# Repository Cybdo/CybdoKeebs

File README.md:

# CybdoKeebs!

A hotswappable ecosystem of i2c powered keyboard modules!

I made this project because I wanted to make something cooler than a macropad, and being able to just swap stuff around seemed really sick.

Inspired by [Ocreeb](https://www.youtube.com/watch?v=7DfexfHzT-w)!

# File structure

everything for each module is found under `modules/[module name]`, including CAD files, EDA files and firmware.

# Features
 - plug and play
 - hotswappable modules
 - exposed I2C buses
 - fully open source!
 - supports any MX-footprint keyswitches!
 - inbuilt USB hub in the controller

# Firmware
Firmware runs on circuitpython, and the firmware for each module is under `modules/[module name]/firmware`. Flash it using the SWD ports on each module, or via USB on the controller hub. You may need a SWD to USB converter, which can be made using a Raspberry Pi Pico.

# Custom modules
Each module is made as a composite of "sub units", each being 6cm tall and 5cm wide, with male pogo pins on the top and left sides, and female recievers on the bottom and right sides. These can be found here: https://www.aliexpress.com/item/1005005284441979.html

# Assembly
Everything is designed to be tray mounted, as to not obstruct the pogo pin assemblies! This means, the plate snaps into and are held up by keyswitches.

To put the keyboard together, put 4 keyswitches in each of the corners of the plate, then put the keyswitches through their sockets. After checking that everything is aligned, put in the rest of the switches!

# BOM
found at `bom.csv`, assuming 1 controller hub, one keyboard and one macropad

# Schematics

## Hub

## Macropad

## Keyboard

# PCB

## Hub

## Macropad

## Keyboard

# Acknowledgements
 - [KiCad](https://www.kicad.org)
 - [Hack Club Fallout](https://fallout.hackclub.com)
 - [Ocreeb V2](https://github.com/sb-ocr/ocreeb-mk-2)
 - [CircuitPython](https://circuitpython.org/)
 - [ai03 Plate Generator](https://kbplate.ai03.com/)
 - [Hack Club Hackpad](https://hackpad.hackclub.com)

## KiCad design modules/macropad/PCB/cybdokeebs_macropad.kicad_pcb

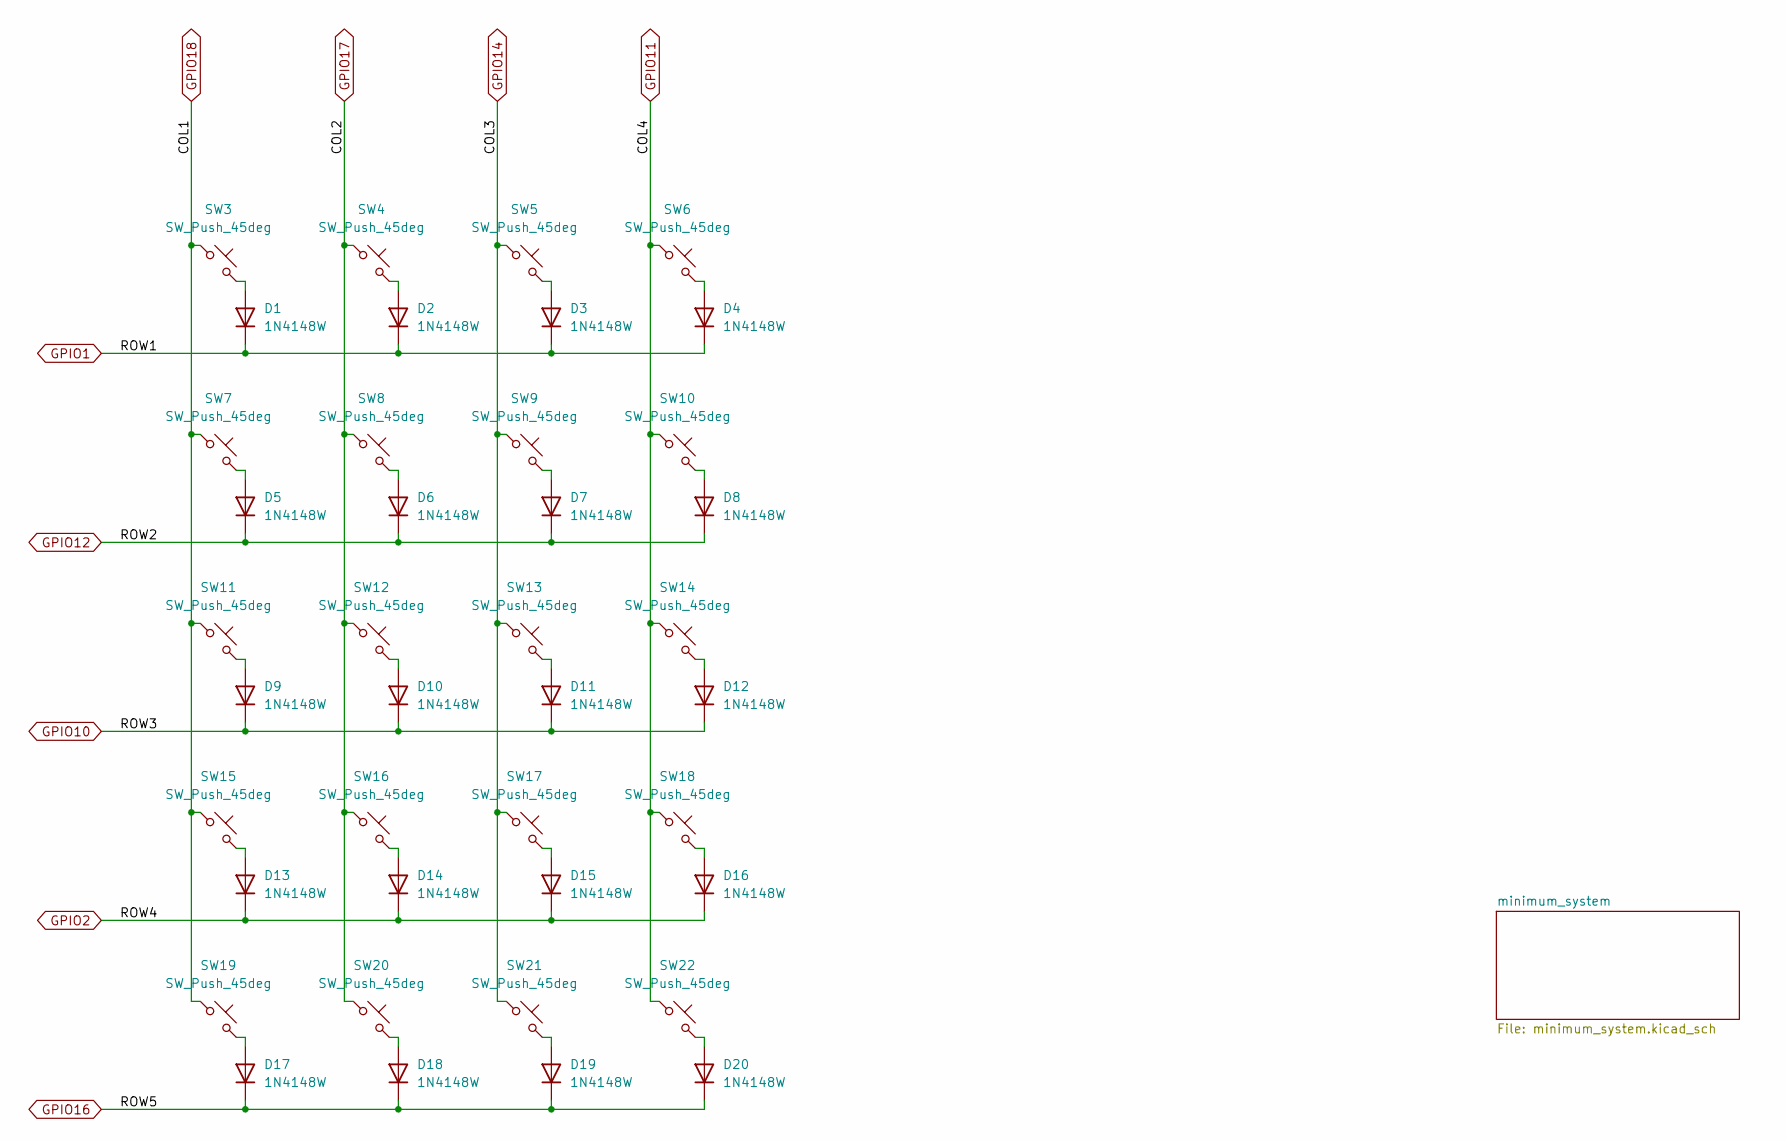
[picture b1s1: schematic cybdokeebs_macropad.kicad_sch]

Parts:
D1, D2, D3, D4, D5, D6, D7, D8, D9, D10, D11, D12, D13, D14, D15, D16, D17, D18, D19, D20: 1N4148W; D_SOD-123
SW3, SW4, SW5, SW6, SW7, SW8, SW9, SW10, SW11, SW12, SW13, SW14, SW15, SW16, SW17, SW18, SW19, SW20, SW21, SW22: SW_Push_45deg; SW_Hotswap_Kailh_MX_1.00u

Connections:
GPIO1: D1.1 (K), D2.1 (K), D3.1 (K), D4.1 (K); also elsewhere on the board
GPIO2: D13.1 (K), D14.1 (K), D15.1 (K), D16.1 (K); also elsewhere on the board
GPIO10: D9.1 (K), D10.1 (K), D11.1 (K), D12.1 (K); also elsewhere on the board
GPIO11: SW6.1, SW10.1, SW14.1, SW18.1, SW22.1; also elsewhere on the board
GPIO12: D5.1 (K), D6.1 (K), D7.1 (K), D8.1 (K); also elsewhere on the board
GPIO14: SW5.1, SW9.1, SW13.1, SW17.1, SW21.1; also elsewhere on the board
GPIO16: D17.1 (K), D18.1 (K), D19.1 (K), D20.1 (K); also elsewhere on the board
GPIO17: SW4.1, SW8.1, SW12.1, SW16.1, SW20.1; also elsewhere on the board
GPIO18: SW3.1, SW7.1, SW11.1, SW15.1, SW19.1; also elsewhere on the board
unnamed: D1.2 (A), SW3.2
unnamed: D2.2 (A), SW4.2
unnamed: D3.2 (A), SW5.2
unnamed: D4.2 (A), SW6.2
unnamed: D5.2 (A), SW7.2
unnamed: D6.2 (A), SW8.2
unnamed: D7.2 (A), SW9.2
unnamed: D8.2 (A), SW10.2
unnamed: D9.2 (A), SW11.2
unnamed: D10.2 (A), SW12.2
unnamed: D11.2 (A), SW13.2
unnamed: D12.2 (A), SW14.2
unnamed: D13.2 (A), SW15.2
unnamed: D14.2 (A), SW16.2
unnamed: D15.2 (A), SW17.2
unnamed: D16.2 (A), SW18.2
unnamed: D17.2 (A), SW19.2
unnamed: D18.2 (A), SW20.2
unnamed: D19.2 (A), SW21.2
unnamed: D20.2 (A), SW22.2

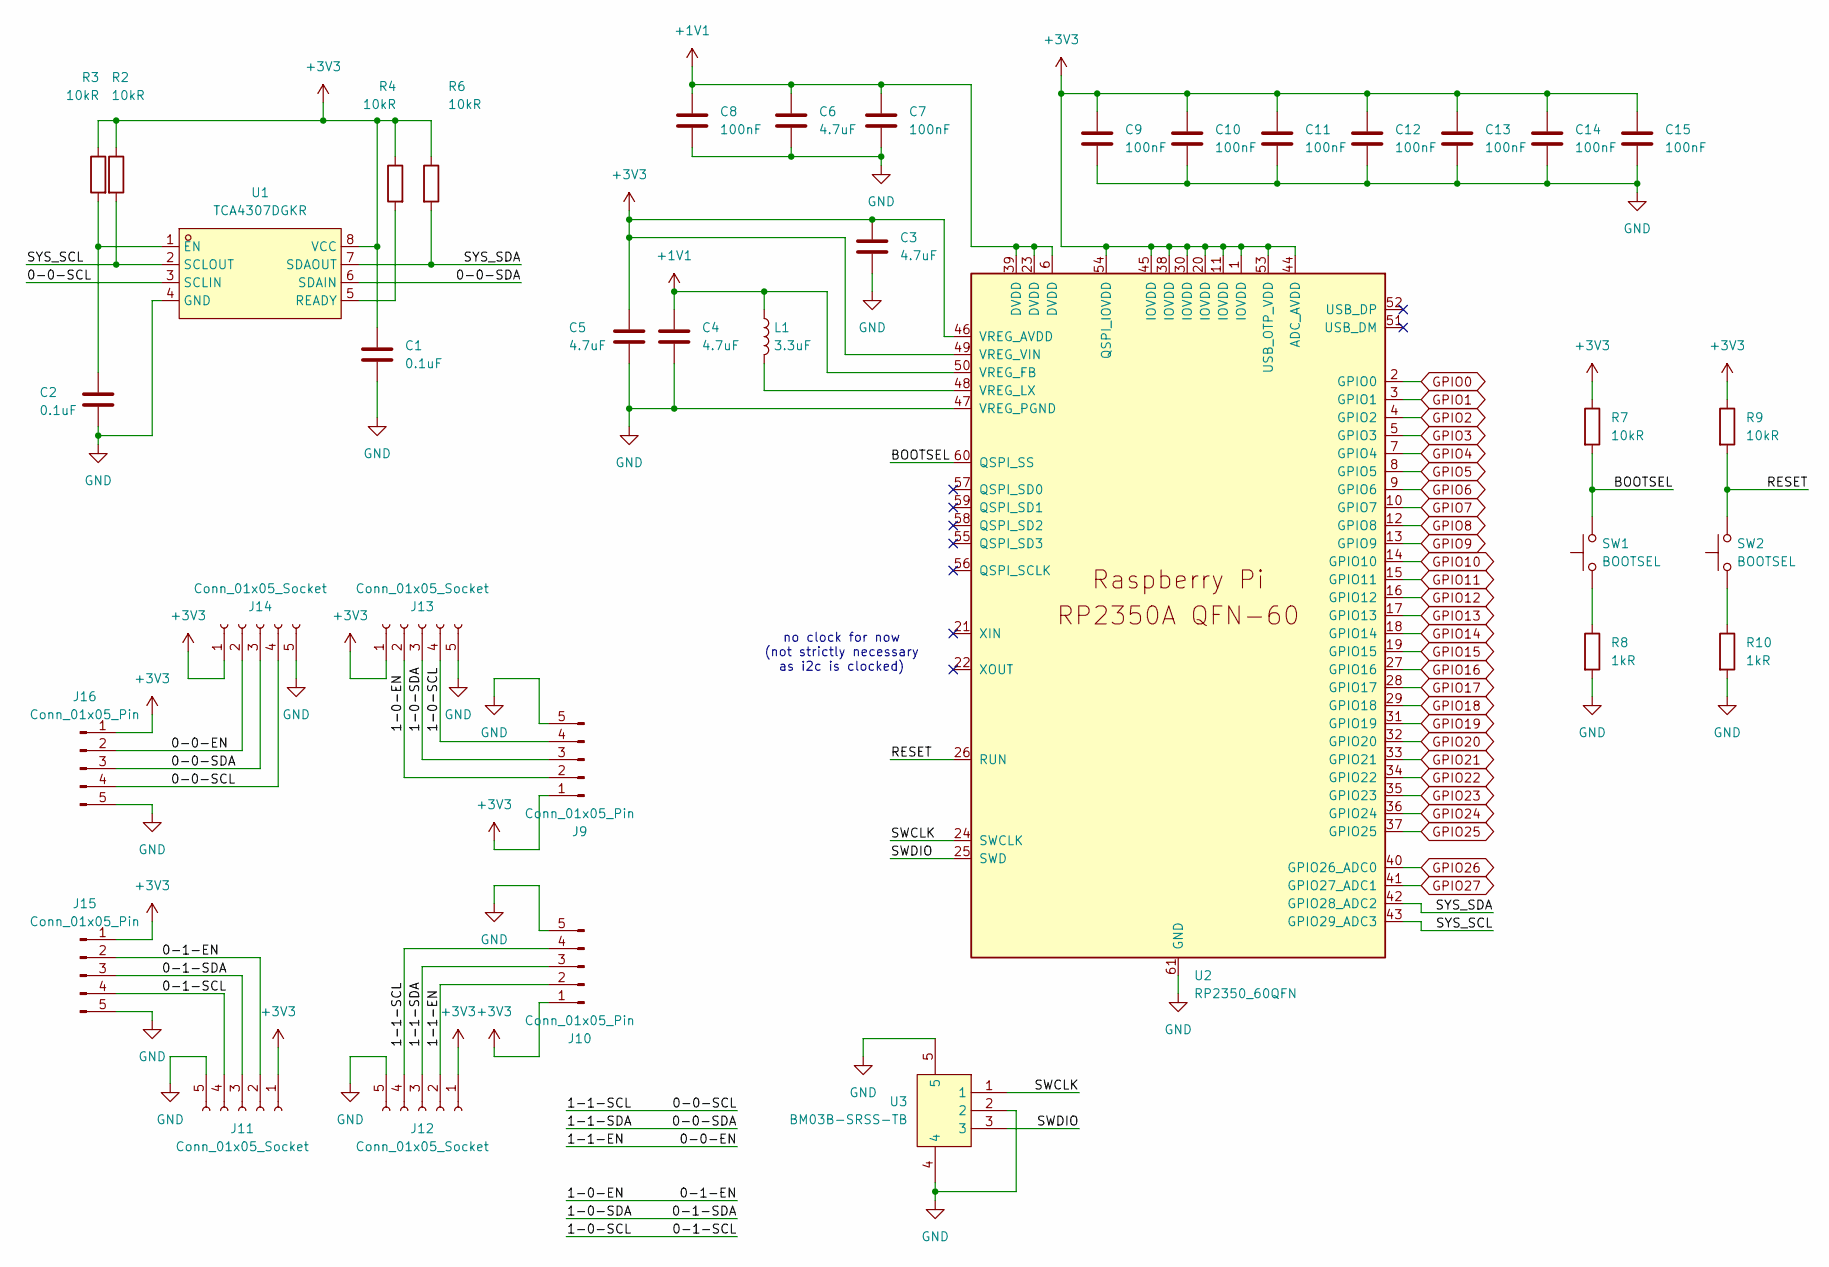
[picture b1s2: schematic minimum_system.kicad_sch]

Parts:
C1, C2: 0.1uF; C_0402_1005Metric_Pad0.74x0.62mm_HandSolder
C3, C4, C5, C6: 4.7uF; C_0402_1005Metric_Pad0.74x0.62mm_HandSolder
C7, C8, C9, C10, C11, C12, C13, C14, C15: 100nF; C_0402_1005Metric_Pad0.74x0.62mm_HandSolder
J9, J10, J15, J16: Conn_01x05_Pin; pogo 5pin 2.54
J11, J12, J13, J14: Conn_01x05_Socket; pogo 5pin 2.54
L1: 3.3uF; INDC1608X95N
R2, R3, R4, R6, R7, R9: 10kR; R_0402_1005Metric_Pad0.72x0.64mm_HandSolder
R8, R10: 1kR; R_0402_1005Metric_Pad0.72x0.64mm_HandSolder
SW1, SW2: BOOTSEL; SW_Push_SPST_NO_Alps_SKRK
U1: TCA4307DGKR; VSSOP-8_L3.0-W3.0-P0.65-LS4.9-BL; MPN TCA4307DGKR; LCSC Part C880333
U2: RP2350_60QFN; RP2350-QFN-60-1EP_7x7_P0.4mm_EP3.4x3.4mm_ThermalVias
U3: BM03B-SRSS-TB; CONN-SMD-3P-P1.00_BM03B-SRSS-TB-LF-SN; MPN BM03B-SRSS-TB(LF)(SN); LCSC Part C160389

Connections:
+1V1: C4.1, C6.1, C7.2, C8.1, L1.1, U2.6 (DVDD), U2.23 (DVDD), U2.39 (DVDD), U2.50 (VREG_FB)
+3V3: C1.1, C3.1, C5.2, C9.2, C10.2, C11.2, C12.2, C13.2, C14.2, C15.2, J9.1, J10.1, J11.1, J12.1, J13.1, J14.1, J15.1, J16.1, R2.1, R3.1, R4.1, R6.1, R7.1, R9.1, U1.8 (VCC), U2.1 (IOVDD), U2.11 (IOVDD), U2.20 (IOVDD), U2.30 (IOVDD), U2.38 (IOVDD), U2.44 (ADC_AVDD), U2.45 (IOVDD), U2.46 (VREG_AVDD), U2.49 (VREG_VIN), U2.53 (USB_OTP_VDD), U2.54 (QSPI_IOVDD)
/minimum_system/0-0-SCL: J10.4, J12.4, J14.4, J16.4, U1.3 (SCLIN)
/minimum_system/0-0-SDA: J10.3, J12.3, J14.3, J16.3, U1.6 (SDAIN)
/minimum_system/0-1-EN: J9.2, J11.2, J13.2, J15.2
/minimum_system/0-1-SCL: J9.4, J11.4, J13.4, J15.4
/minimum_system/0-1-SDA: J9.3, J11.3, J13.3, J15.3
/minimum_system/BOOTSEL: R7.2, SW1.2, U2.60 (QSPI_SS)
/minimum_system/RESET: R9.2, SW2.2, U2.26 (RUN)
/minimum_system/SWCLK: U2.24 (SWCLK), U3.1
/minimum_system/SWDIO: U2.25 (SWD), U3.3
/minimum_system/SYS_SCL: R2.2, U1.2 (SCLOUT), U2.43 (GPIO29_ADC3)
/minimum_system/SYS_SDA: R6.2, U1.7 (SDAOUT), U2.42 (GPIO28_ADC2)
GND: C1.2, C2.2, C3.2, C4.2, C5.1, C6.2, C7.1, C8.2, C9.1, C10.1, C11.1, C12.1, C13.1, C14.1, C15.1, J9.5, J10.5, J11.5, J12.5, J13.5, J14.5, J15.5, J16.5, R8.2, R10.2, U1.4 (GND), U2.47 (VREG_PGND), U2.61 (GND), U3.2, U3.4, U3.5
GPIO0: U2.2 (GPIO0)
GPIO1: U2.3 (GPIO1); also elsewhere on the board
GPIO2: U2.4 (GPIO2); also elsewhere on the board
GPIO3: U2.5 (GPIO3)
GPIO4: U2.7 (GPIO4)
GPIO5: U2.8 (GPIO5)
GPIO6: U2.9 (GPIO6)
GPIO7: U2.10 (GPIO7)
GPIO8: U2.12 (GPIO8)
GPIO9: U2.13 (GPIO9)
GPIO10: U2.14 (GPIO10); also elsewhere on the board
GPIO11: U2.15 (GPIO11); also elsewhere on the board
GPIO12: U2.16 (GPIO12); also elsewhere on the board
GPIO13: U2.17 (GPIO13)
GPIO14: U2.18 (GPIO14); also elsewhere on the board
GPIO15: U2.19 (GPIO15)
GPIO16: U2.27 (GPIO16); also elsewhere on the board
GPIO17: U2.28 (GPIO17); also elsewhere on the board
GPIO18: U2.29 (GPIO18); also elsewhere on the board
GPIO19: U2.31 (GPIO19)
GPIO20: U2.32 (GPIO20)
GPIO21: U2.33 (GPIO21)
GPIO23: U2.35 (GPIO23)
GPIO24: U2.36 (GPIO24)
GPIO25: U2.37 (GPIO25)
GPIO26: U2.40 (GPIO26_ADC0)
GPIO27: U2.41 (GPIO27_ADC1)
unnamed: R8.1, SW1.1
unnamed: R10.1, SW2.1
unnamed: C2.1, R3.2, U1.1 (EN)
unnamed: R4.2, U1.5 (READY)
unnamed: L1.2, U2.48 (VREG_LX)

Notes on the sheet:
no clock for now (not strictly necessary as i2c is clocked)

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
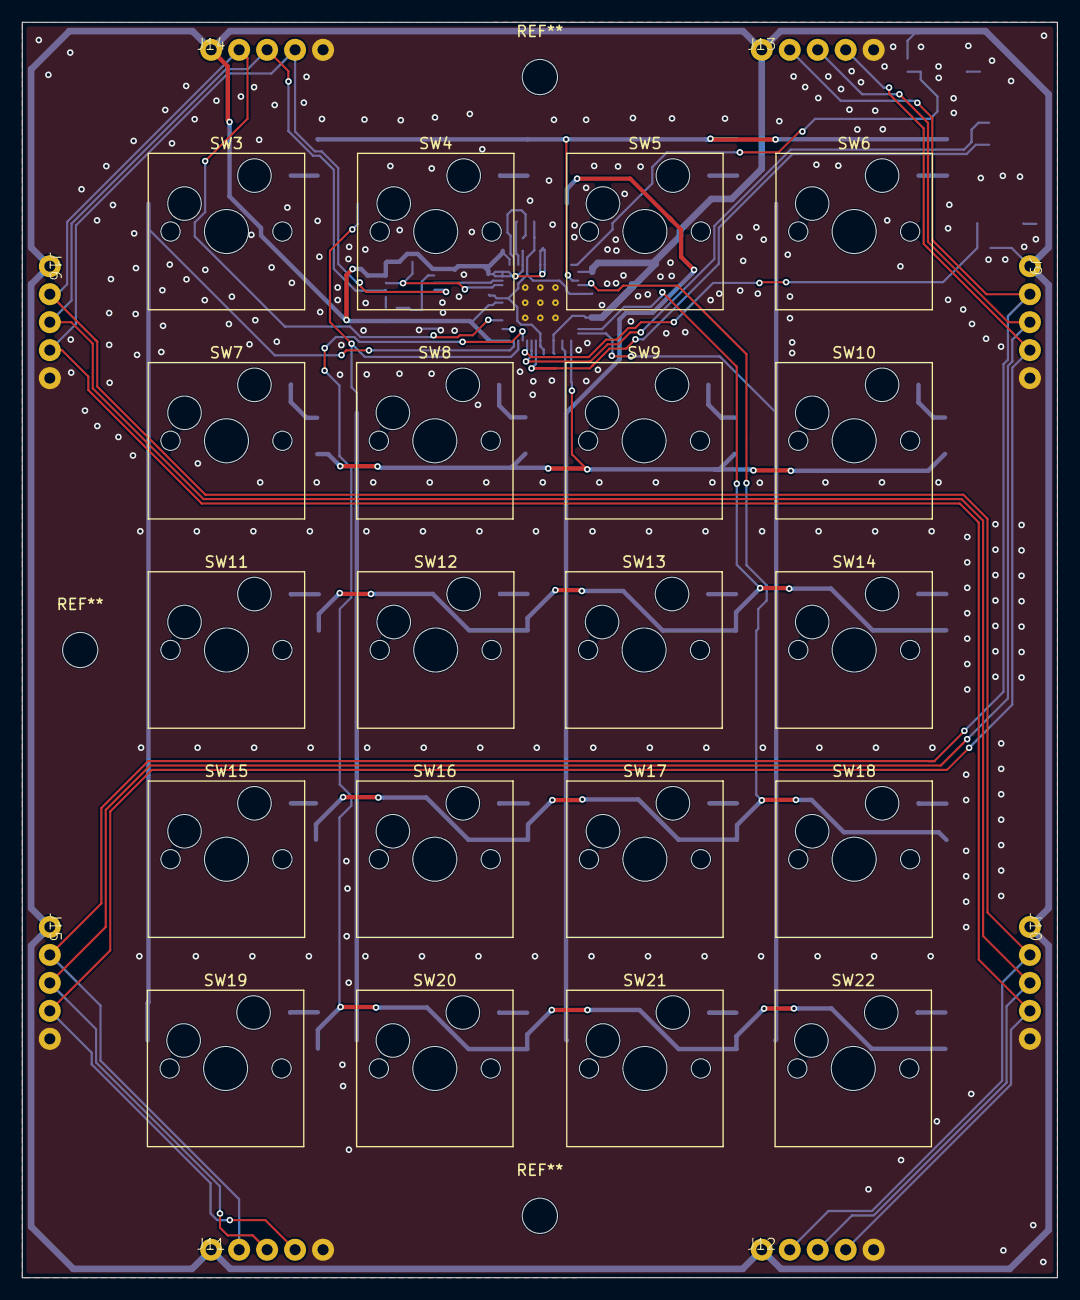
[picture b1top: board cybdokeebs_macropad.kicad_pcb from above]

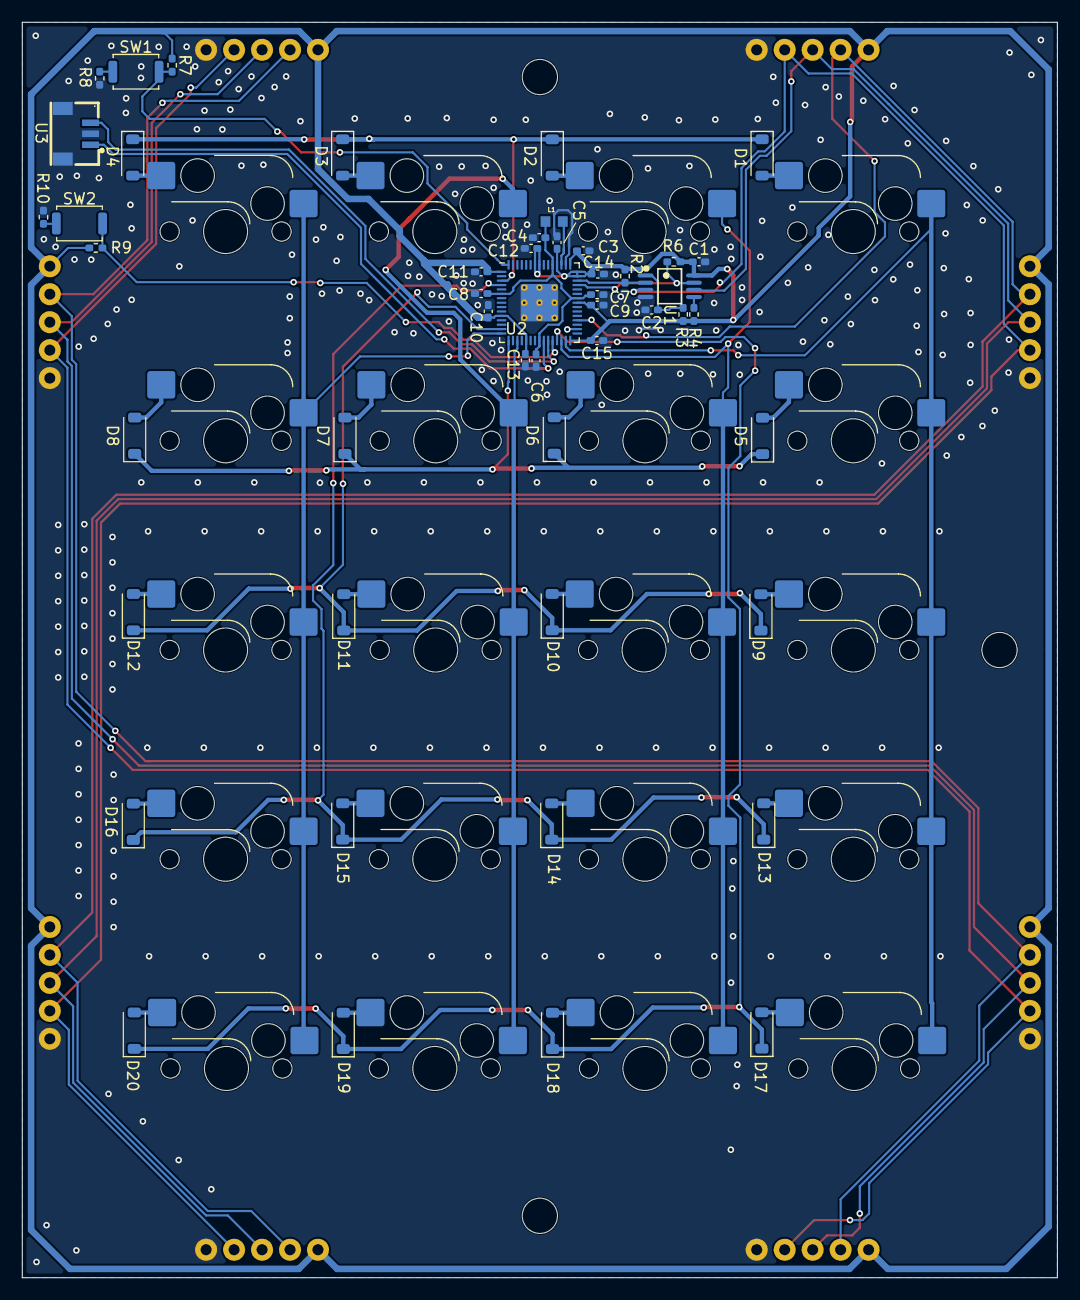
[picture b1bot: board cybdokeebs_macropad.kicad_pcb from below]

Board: 2 copper layers, 94.0 x 114.0 mm, 77 parts (49 on the bottom side), 49 nets.

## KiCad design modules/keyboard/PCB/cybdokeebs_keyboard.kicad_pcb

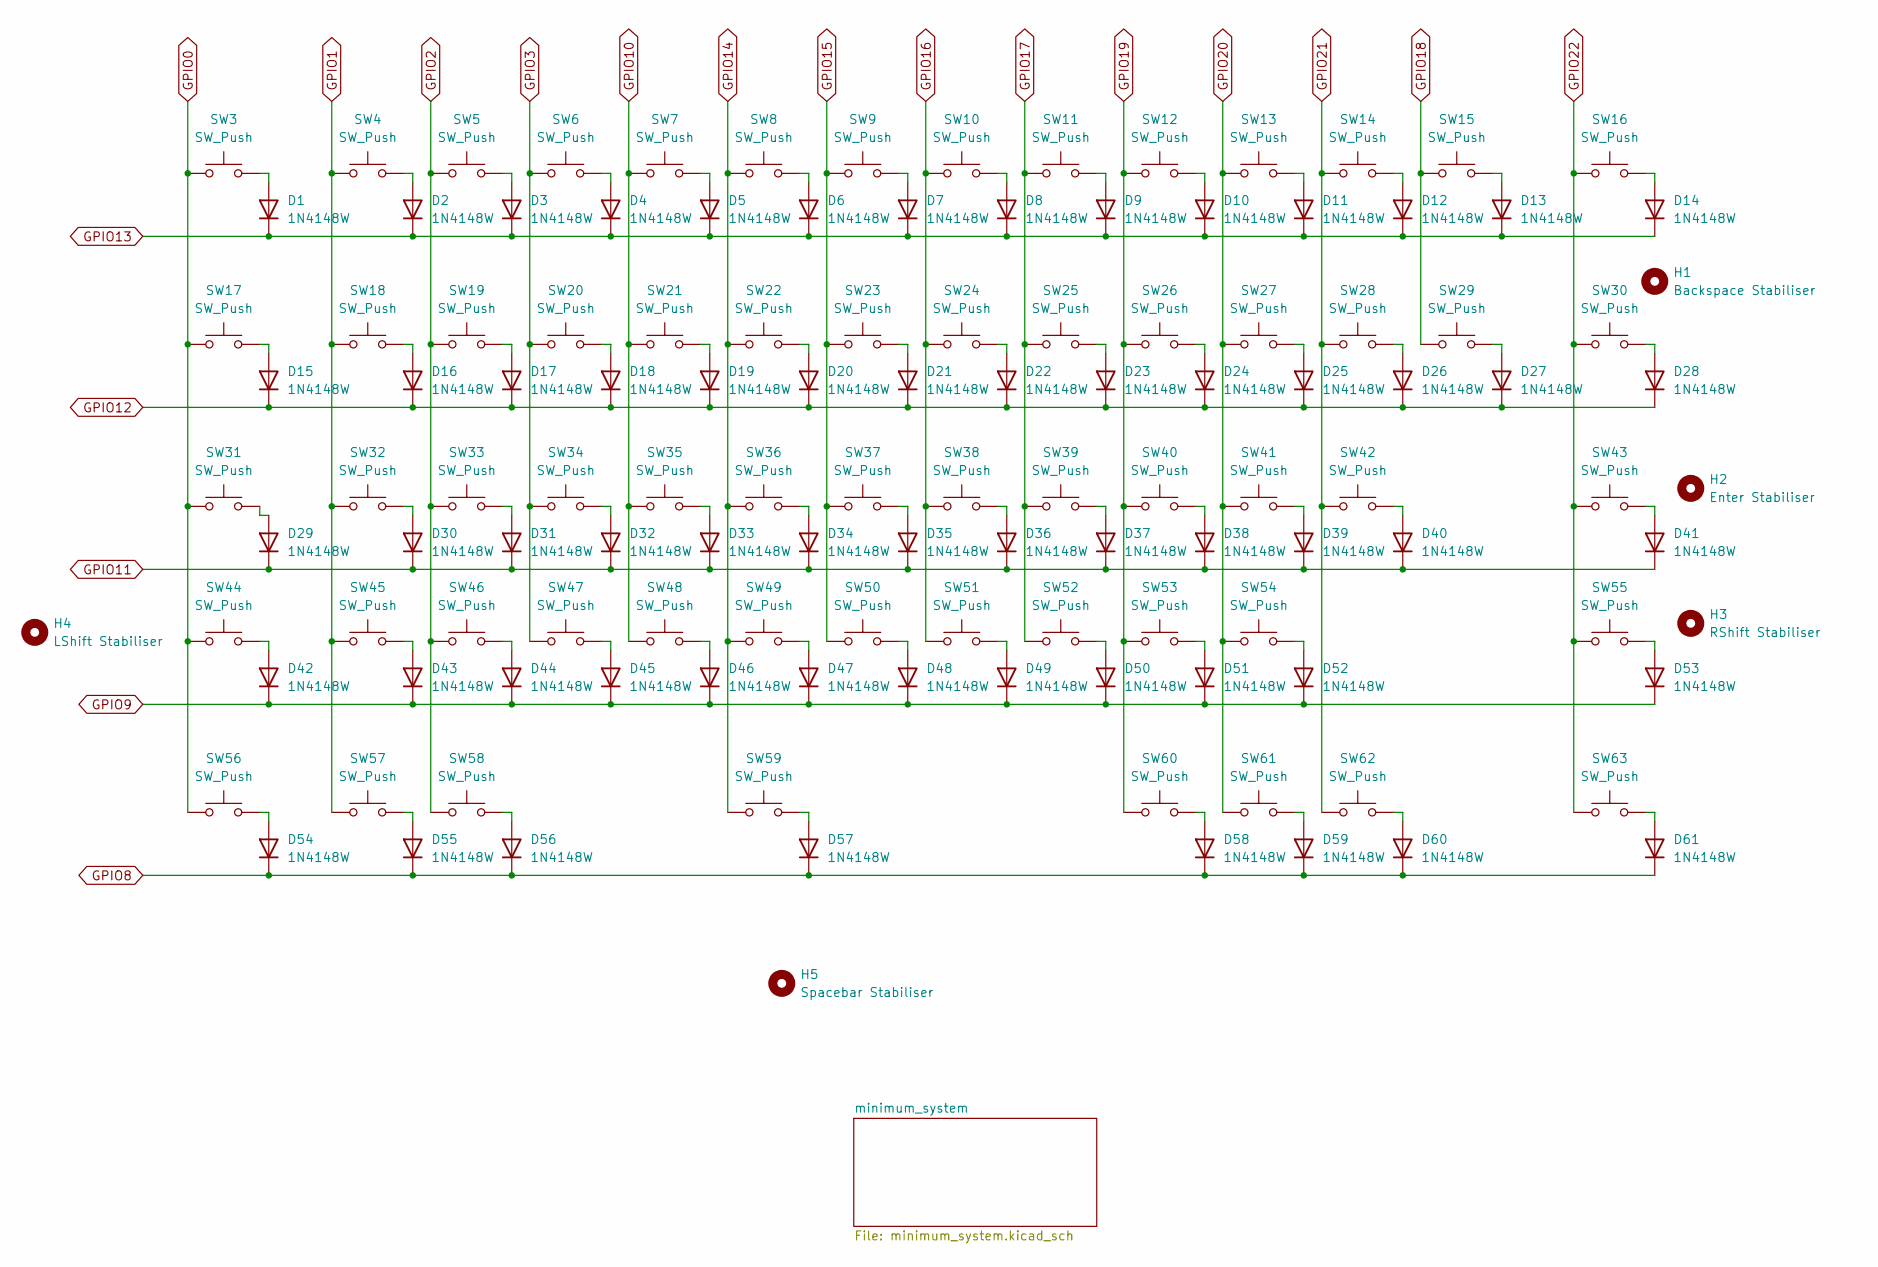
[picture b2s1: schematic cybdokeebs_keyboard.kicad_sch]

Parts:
D1, D2, D3, D4, D5, D6, D7, D8, D9, D10, D11, D12, D13, D14, D15, D16, D17, D18, D19, D20, D21, D22, D23, D24, D25, D26, D27, D28, D29, D30, D31, D32, D33, D34, D35, D36, D37, D38, D39, D40, D41, D42, D43, D44, D45, D46, D47, D48, D49, D50, D51, D52, D53, D54, D55, D56, D57, D58, D59, D60, D61: 1N4148W; D_SOD-123
H1: Backspace Stabiliser; Stabilizer_Cherry_MX_2.00u
H2: Enter Stabiliser; Stabilizer_Cherry_MX_2.00u
H3: RShift Stabiliser; Stabilizer_Cherry_MX_2.00u
H4: LShift Stabiliser; Stabilizer_Cherry_MX_2.00u
H5: Spacebar Stabiliser; Stabilizer_Cherry_MX_6.25u
SW3, SW4, SW5, SW6, SW7, SW8, SW9, SW10, SW11, SW12, SW13, SW14, SW15, SW18, SW19, SW20, SW21, SW22, SW23, SW24, SW25, SW26, SW27, SW28, SW29, SW32, SW33, SW34, SW35, SW36, SW37, SW38, SW39, SW40, SW41, SW42, SW45, SW46, SW47, SW48, SW49, SW50, SW51, SW52, SW53, SW54: SW_Push; SW_Hotswap_Kailh_MX_1.00u
SW16: SW_Push; SW_Hotswap_Kailh_MX_2.00u
SW17, SW30: SW_Push; SW_Hotswap_Kailh_MX_1.50u
SW31: SW_Push; SW_Hotswap_Kailh_MX_1.75u
SW43, SW44: SW_Push; SW_Hotswap_Kailh_MX_2.25u
SW55: SW_Push; SW_Hotswap_Kailh_MX_2.75u
SW56, SW57, SW58, SW60, SW61, SW62, SW63: SW_Push; SW_Hotswap_Kailh_MX_1.25u
SW59: SW_Push; SW_Hotswap_Kailh_MX_6.25u

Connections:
GPIO0: SW3.1, SW17.1, SW31.1, SW44.1, SW56.1; also elsewhere on the board
GPIO1: SW4.1, SW18.1, SW32.1, SW45.1, SW57.1; also elsewhere on the board
GPIO2: SW5.1, SW19.1, SW33.1, SW46.1, SW58.1; also elsewhere on the board
GPIO3: SW6.1, SW20.1, SW34.1, SW47.1; also elsewhere on the board
GPIO8: D54.1 (K), D55.1 (K), D56.1 (K), D57.1 (K), D58.1 (K), D59.1 (K), D60.1 (K), D61.1 (K); also elsewhere on the board
GPIO9: D42.1 (K), D43.1 (K), D44.1 (K), D45.1 (K), D46.1 (K), D47.1 (K), D48.1 (K), D49.1 (K), D50.1 (K), D51.1 (K), D52.1 (K), D53.1 (K); also elsewhere on the board
GPIO10: SW7.1, SW21.1, SW35.1, SW48.1; also elsewhere on the board
GPIO11: D29.1 (K), D30.1 (K), D31.1 (K), D32.1 (K), D33.1 (K), D34.1 (K), D35.1 (K), D36.1 (K), D37.1 (K), D38.1 (K), D39.1 (K), D40.1 (K), D41.1 (K); also elsewhere on the board
GPIO12: D15.1 (K), D16.1 (K), D17.1 (K), D18.1 (K), D19.1 (K), D20.1 (K), D21.1 (K), D22.1 (K), D23.1 (K), D24.1 (K), D25.1 (K), D26.1 (K), D27.1 (K), D28.1 (K); also elsewhere on the board
GPIO13: D1.1 (K), D2.1 (K), D3.1 (K), D4.1 (K), D5.1 (K), D6.1 (K), D7.1 (K), D8.1 (K), D9.1 (K), D10.1 (K), D11.1 (K), D12.1 (K), D13.1 (K), D14.1 (K); also elsewhere on the board
GPIO14: SW8.1, SW22.1, SW36.1, SW49.1, SW59.1; also elsewhere on the board
GPIO15: SW9.1, SW23.1, SW37.1, SW50.1; also elsewhere on the board
GPIO16: SW10.1, SW24.1, SW38.1, SW51.1; also elsewhere on the board
GPIO17: SW11.1, SW25.1, SW39.1, SW52.1; also elsewhere on the board
GPIO18: SW15.1, SW29.1; also elsewhere on the board
GPIO19: SW12.1, SW26.1, SW40.1, SW53.1, SW60.1; also elsewhere on the board
GPIO20: SW13.1, SW27.1, SW41.1, SW54.1, SW61.1; also elsewhere on the board
GPIO21: SW14.1, SW28.1, SW42.1, SW62.1; also elsewhere on the board
GPIO22: SW16.1, SW30.1, SW43.1, SW55.1, SW63.1; also elsewhere on the board
unnamed: D1.2 (A), SW3.2
unnamed: D2.2 (A), SW4.2
unnamed: D3.2 (A), SW5.2
unnamed: D4.2 (A), SW6.2
unnamed: D5.2 (A), SW7.2
unnamed: D6.2 (A), SW8.2
unnamed: D7.2 (A), SW9.2
unnamed: D8.2 (A), SW10.2
unnamed: D9.2 (A), SW11.2
unnamed: D10.2 (A), SW12.2
unnamed: D11.2 (A), SW13.2
unnamed: D12.2 (A), SW14.2
unnamed: D13.2 (A), SW15.2
unnamed: D14.2 (A), SW16.2
unnamed: D15.2 (A), SW17.2
unnamed: D16.2 (A), SW18.2
unnamed: D17.2 (A), SW19.2
unnamed: D18.2 (A), SW20.2
unnamed: D19.2 (A), SW21.2
unnamed: D20.2 (A), SW22.2
unnamed: D21.2 (A), SW23.2
unnamed: D22.2 (A), SW24.2
unnamed: D23.2 (A), SW25.2
unnamed: D24.2 (A), SW26.2
unnamed: D25.2 (A), SW27.2
unnamed: D26.2 (A), SW28.2
unnamed: D27.2 (A), SW29.2
unnamed: D28.2 (A), SW30.2
unnamed: D29.2 (A), SW31.2
unnamed: D30.2 (A), SW32.2
unnamed: D31.2 (A), SW33.2
unnamed: D32.2 (A), SW34.2
unnamed: D33.2 (A), SW35.2
unnamed: D34.2 (A), SW36.2
unnamed: D35.2 (A), SW37.2
unnamed: D36.2 (A), SW38.2
unnamed: D37.2 (A), SW39.2
unnamed: D38.2 (A), SW40.2
unnamed: D39.2 (A), SW41.2
unnamed: D40.2 (A), SW42.2
unnamed: D41.2 (A), SW43.2
unnamed: D42.2 (A), SW44.2
unnamed: D43.2 (A), SW45.2
unnamed: D44.2 (A), SW46.2
unnamed: D45.2 (A), SW47.2
unnamed: D46.2 (A), SW48.2
unnamed: D47.2 (A), SW49.2
unnamed: D48.2 (A), SW50.2
unnamed: D49.2 (A), SW51.2
unnamed: D50.2 (A), SW52.2
unnamed: D51.2 (A), SW53.2
unnamed: D52.2 (A), SW54.2
unnamed: D53.2 (A), SW55.2
unnamed: D54.2 (A), SW56.2
unnamed: D55.2 (A), SW57.2
unnamed: D56.2 (A), SW58.2
unnamed: D57.2 (A), SW59.2
unnamed: D58.2 (A), SW60.2
unnamed: D59.2 (A), SW61.2
unnamed: D60.2 (A), SW62.2
unnamed: D61.2 (A), SW63.2

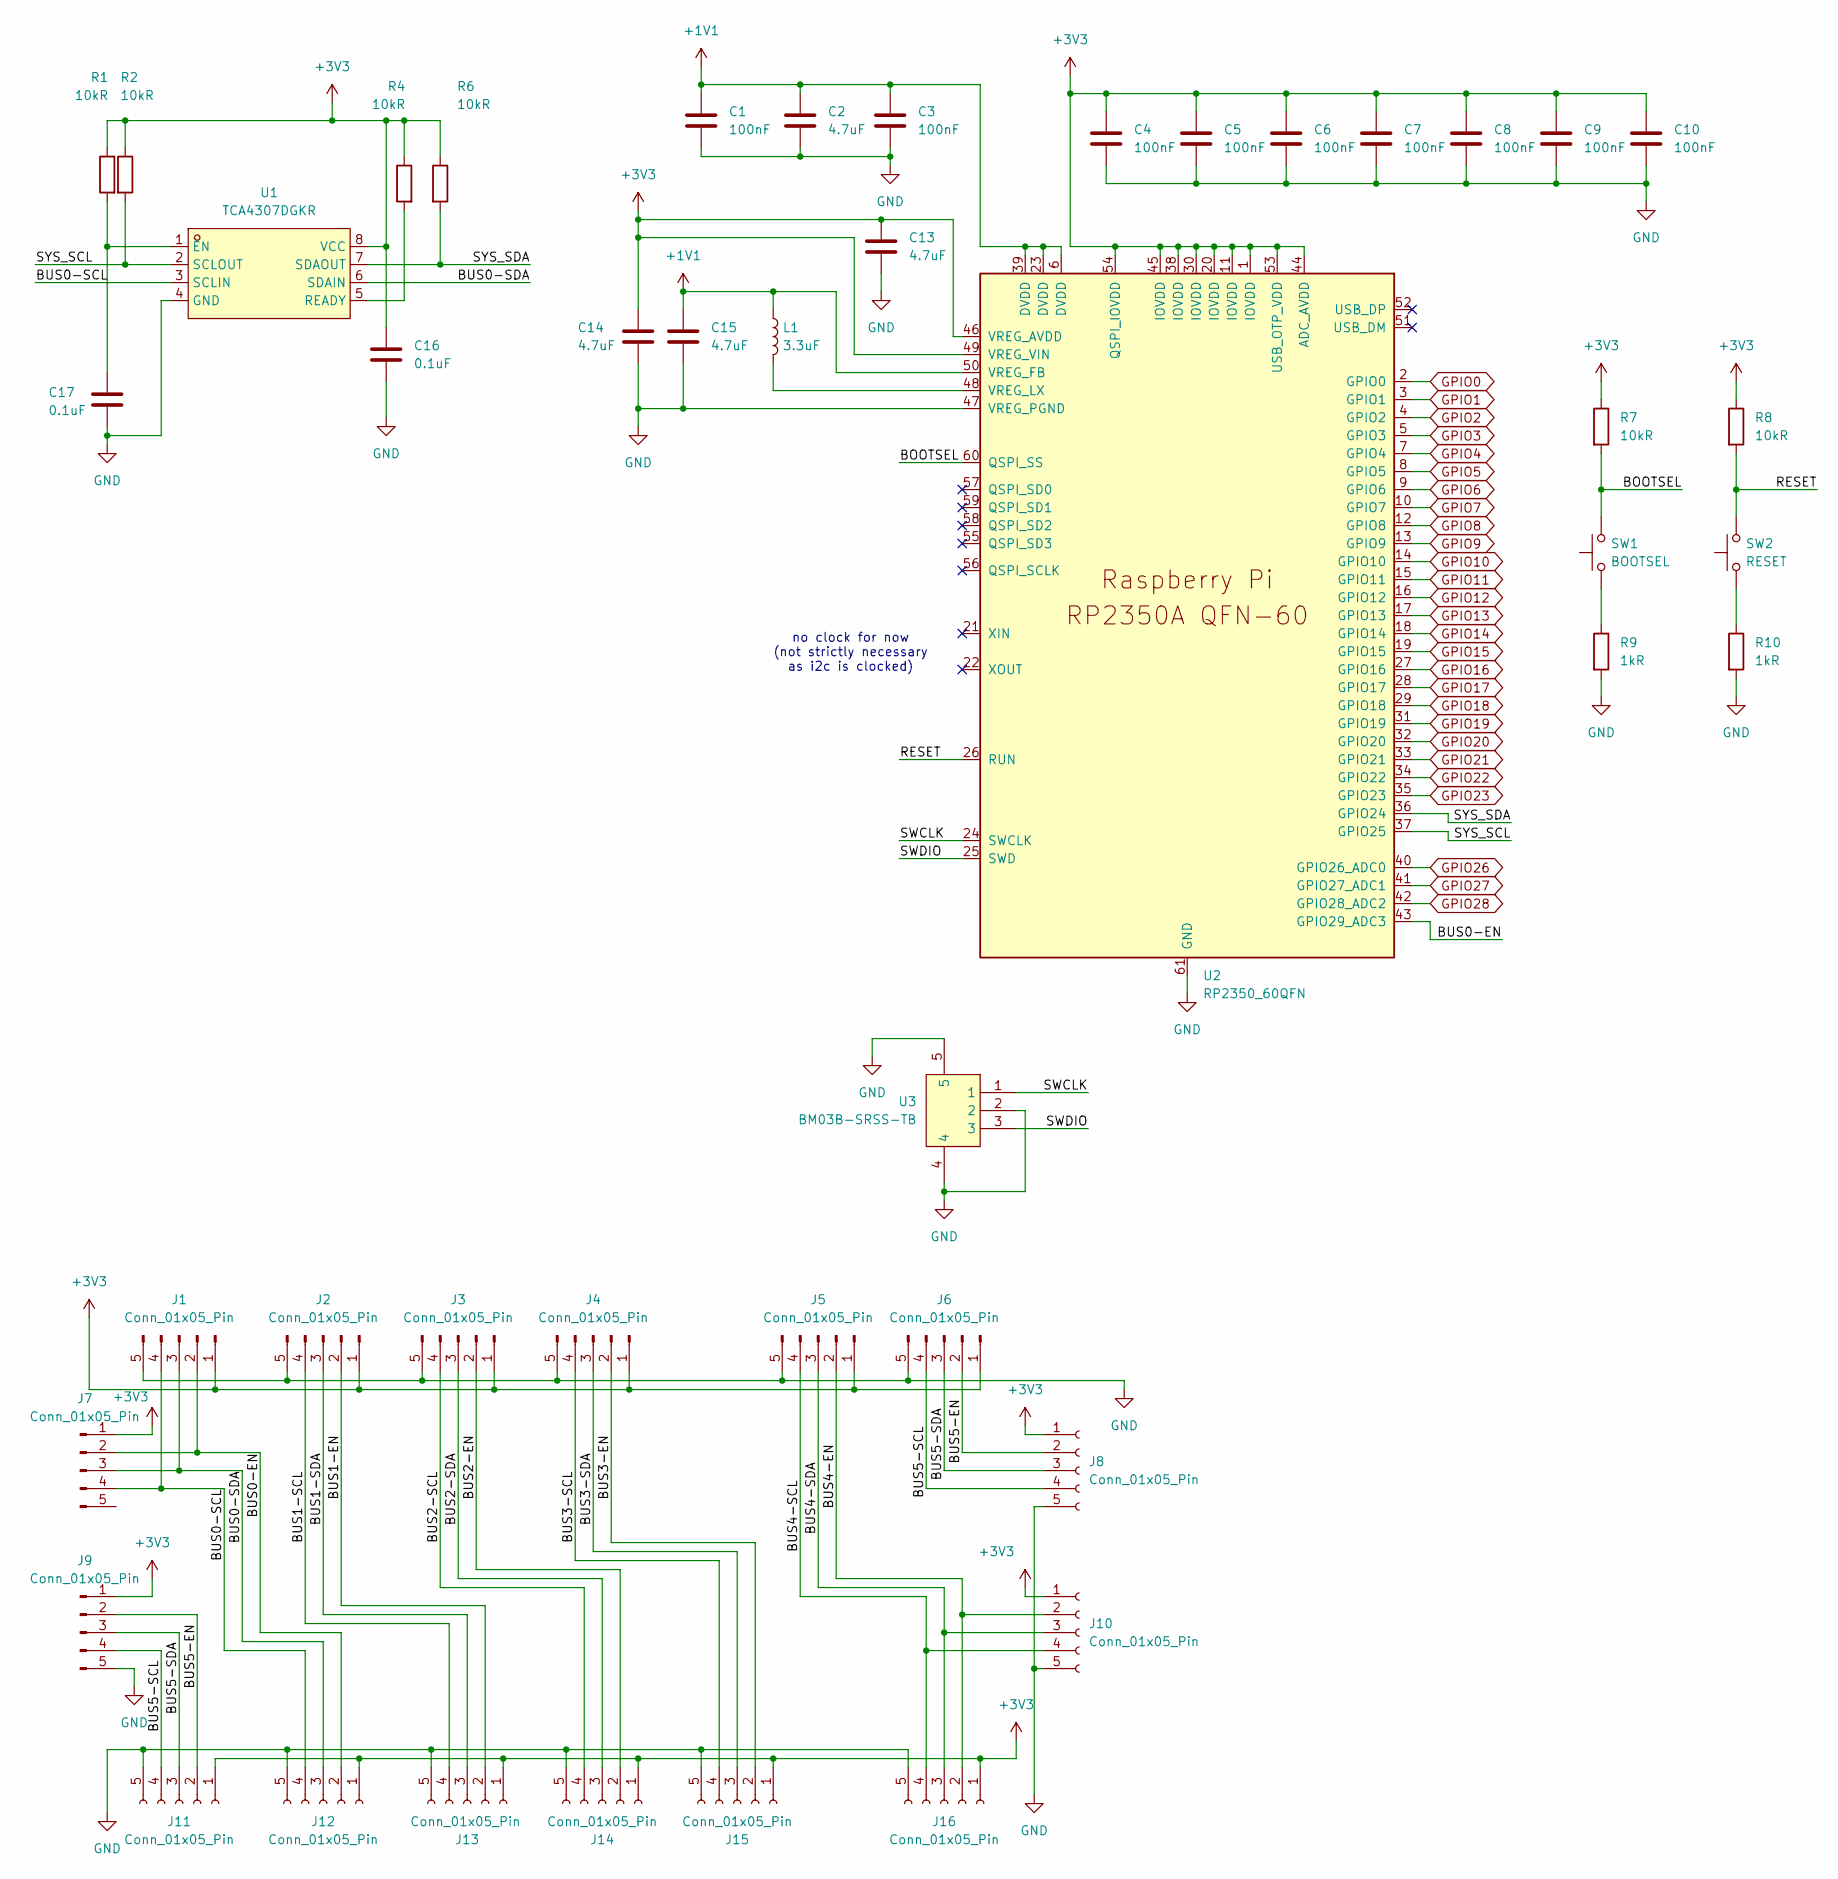
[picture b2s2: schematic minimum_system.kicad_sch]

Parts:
C1, C3, C4, C5, C6, C7, C8, C9, C10: 100nF; C_0402_1005Metric_Pad0.74x0.62mm_HandSolder
C2, C13, C14, C15: 4.7uF; C_0402_1005Metric_Pad0.74x0.62mm_HandSolder
C16, C17: 0.1uF; C_0402_1005Metric_Pad0.74x0.62mm_HandSolder
J1, J2, J3, J4, J5, J6, J7, J8, J9, J10, J11, J12, J13, J14, J15, J16: Conn_01x05_Pin; pogo 5pin 2.54
L1: 3.3uF; INDC1608X95N
R1, R2, R4, R6, R7, R8: 10kR; R_0402_1005Metric_Pad0.72x0.64mm_HandSolder
R9, R10: 1kR; R_0402_1005Metric_Pad0.72x0.64mm_HandSolder
SW1: BOOTSEL; SW_Push_SPST_NO_Alps_SKRK
SW2: RESET; SW_Push_SPST_NO_Alps_SKRK
U1: TCA4307DGKR; VSSOP-8_L3.0-W3.0-P0.65-LS4.9-BL; MPN TCA4307DGKR; LCSC Part C880333
U2: RP2350_60QFN; RP2350-QFN-60-1EP_7x7_P0.4mm_EP3.4x3.4mm_ThermalVias
U3: BM03B-SRSS-TB; CONN-SMD-3P-P1.00_BM03B-SRSS-TB-LF-SN; MPN BM03B-SRSS-TB(LF)(SN); LCSC Part C160389

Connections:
+1V1: C1.1, C2.1, C3.2, C15.1, L1.1, U2.6 (DVDD), U2.23 (DVDD), U2.39 (DVDD), U2.50 (VREG_FB)
+3V3: C4.2, C5.2, C6.2, C7.2, C8.2, C9.2, C10.2, C13.1, C14.2, C16.1, J1.1, J2.1, J3.1, J4.1, J5.1, J6.1, J7.1, J8.1, J9.1, J10.1, J11.1, J12.1, J13.1, J14.1, J15.1, J16.1, R1.1, R2.1, R4.1, R6.1, R7.1, R8.1, U1.8 (VCC), U2.1 (IOVDD), U2.11 (IOVDD), U2.20 (IOVDD), U2.30 (IOVDD), U2.38 (IOVDD), U2.44 (ADC_AVDD), U2.45 (IOVDD), U2.46 (VREG_AVDD), U2.49 (VREG_VIN), U2.53 (USB_OTP_VDD), U2.54 (QSPI_IOVDD)
/minimum_system/BOOTSEL: R7.2, SW1.2, U2.60 (QSPI_SS)
/minimum_system/BUS0-EN: J1.2, J7.2, J12.2, U2.43 (GPIO29_ADC3)
/minimum_system/BUS0-SCL: J1.4, J7.4, J12.4, U1.3 (SCLIN)
/minimum_system/BUS0-SDA: J1.3, J7.3, J12.3, U1.6 (SDAIN)
/minimum_system/BUS1-EN: J2.2, J13.2
/minimum_system/BUS1-SCL: J2.4, J13.4
/minimum_system/BUS1-SDA: J2.3, J13.3
/minimum_system/BUS2-EN: J3.2, J14.2
/minimum_system/BUS2-SCL: J3.4, J14.4
/minimum_system/BUS2-SDA: J3.3, J14.3
/minimum_system/BUS3-EN: J4.2, J15.2
/minimum_system/BUS3-SCL: J4.4, J15.4
/minimum_system/BUS3-SDA: J4.3, J15.3
/minimum_system/BUS4-EN: J5.2, J10.2, J16.2
/minimum_system/BUS4-SCL: J5.4, J10.4, J16.4
/minimum_system/BUS4-SDA: J5.3, J10.3, J16.3
/minimum_system/BUS5-EN: J6.2, J8.2, J9.2, J11.2
/minimum_system/BUS5-SCL: J6.4, J8.4, J9.4, J11.4
/minimum_system/BUS5-SDA: J6.3, J8.3, J9.3, J11.3
/minimum_system/RESET: R8.2, SW2.2, U2.26 (RUN)
/minimum_system/SWCLK: U2.24 (SWCLK), U3.1
/minimum_system/SWDIO: U2.25 (SWD), U3.3
/minimum_system/SYS_SCL: R2.2, U1.2 (SCLOUT), U2.37 (GPIO25)
/minimum_system/SYS_SDA: R6.2, U1.7 (SDAOUT), U2.36 (GPIO24)
GND: C1.2, C2.2, C3.1, C4.1, C5.1, C6.1, C7.1, C8.1, C9.1, C10.1, C13.2, C14.1, C15.2, C16.2, C17.2, J1.5, J2.5, J3.5, J4.5, J5.5, J6.5, J8.5, J9.5, J10.5, J11.5, J12.5, J13.5, J14.5, J15.5, J16.5, R9.2, R10.2, U1.4 (GND), U2.47 (VREG_PGND), U2.61 (GND), U3.2, U3.4, U3.5
GPIO0: U2.2 (GPIO0); also elsewhere on the board
GPIO1: U2.3 (GPIO1); also elsewhere on the board
GPIO2: U2.4 (GPIO2); also elsewhere on the board
GPIO3: U2.5 (GPIO3); also elsewhere on the board
GPIO4: U2.7 (GPIO4)
GPIO5: U2.8 (GPIO5)
GPIO6: U2.9 (GPIO6)
GPIO7: U2.10 (GPIO7)
GPIO8: U2.12 (GPIO8); also elsewhere on the board
GPIO9: U2.13 (GPIO9); also elsewhere on the board
GPIO10: U2.14 (GPIO10); also elsewhere on the board
GPIO11: U2.15 (GPIO11); also elsewhere on the board
GPIO12: U2.16 (GPIO12); also elsewhere on the board
GPIO13: U2.17 (GPIO13); also elsewhere on the board
GPIO14: U2.18 (GPIO14); also elsewhere on the board
GPIO15: U2.19 (GPIO15); also elsewhere on the board
GPIO16: U2.27 (GPIO16); also elsewhere on the board
GPIO17: U2.28 (GPIO17); also elsewhere on the board
GPIO18: U2.29 (GPIO18); also elsewhere on the board
GPIO19: U2.31 (GPIO19); also elsewhere on the board
GPIO20: U2.32 (GPIO20); also elsewhere on the board
GPIO21: U2.33 (GPIO21); also elsewhere on the board
GPIO22: U2.34 (GPIO22); also elsewhere on the board
GPIO23: U2.35 (GPIO23)
GPIO26: U2.40 (GPIO26_ADC0)
GPIO27: U2.41 (GPIO27_ADC1)
GPIO28: U2.42 (GPIO28_ADC2)
unnamed: R9.1, SW1.1
unnamed: R10.1, SW2.1
unnamed: C17.1, R1.2, U1.1 (EN)
unnamed: R4.2, U1.5 (READY)
unnamed: L1.2, U2.48 (VREG_LX)

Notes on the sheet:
no clock for now (not strictly necessary as i2c is clocked)
